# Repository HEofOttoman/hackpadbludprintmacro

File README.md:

# HenryWau's BludPad

* Keyboard Maintainer: [Henry Wauzivuff](https://github.com/heofottoman)

This is my very first macropad (and hardware project!) made for Hackpad. I designed it to be optimised for my little desk, being long and narrow, and also having a pretty cool pcb :>

Currently, the firmware binds the keys to Ctrl Z, numpad 1,3,7 & mswhl up/down, designed to help me with creative software, Blender specifically.

## Specifications
### BOM
- 1x Seeed Xiao RP4020
- 1x EC11 Rotary Encoder
- 4x Cherry MX switches
- 4x Blank Keycaps
- 4x SK6812 MINI-E LEDs
- 4x Screws

### Others
- Custom PCB
- QMK Firmware
- Case.STL

### Schematic
 
https://cdn.hackclub.com/019d466b-ad1f-7994-9d12-ee104b858810/image.png

### PCB

Dimensions at max: 38.496 x 97.794 mm
Top left corner to USB - 7.452 mm

Keyhole dimensions:
x = 2.635
y = 0.233

### Case

## References 
A list of the resources I used to hopefully help others and keep their own piece of sanity where I've lost it..

- [Xiao RP2040 Pin Reference](https://wiki.seeedstudio.com/XIAO-RP2040/) - Used the GPIO pins in the table provided for firmware code 
- [Legacy Blueprint Hackpad Guide](https://web.archive.org/web/20251224215247/https://blueprint.hackclub.com/hackpad/index.md) - https://web.archive.org/web/20251224215247/https://blueprint.hackclub.com/hackpad/index.md
- [Porting your keyboard to qmk](https://docs.qmk.fm/porting_your_keyboard_to_qmk)
- [Hackpad Github](https://github.com/hackclub/hackpad/) - Filled with examples of other macropads
- For the plate: [Keyboard Layout Editor](https://www.keyboard-layout-editor.com) & [Ai03's plate editor](https://kbplate.ai03.com)

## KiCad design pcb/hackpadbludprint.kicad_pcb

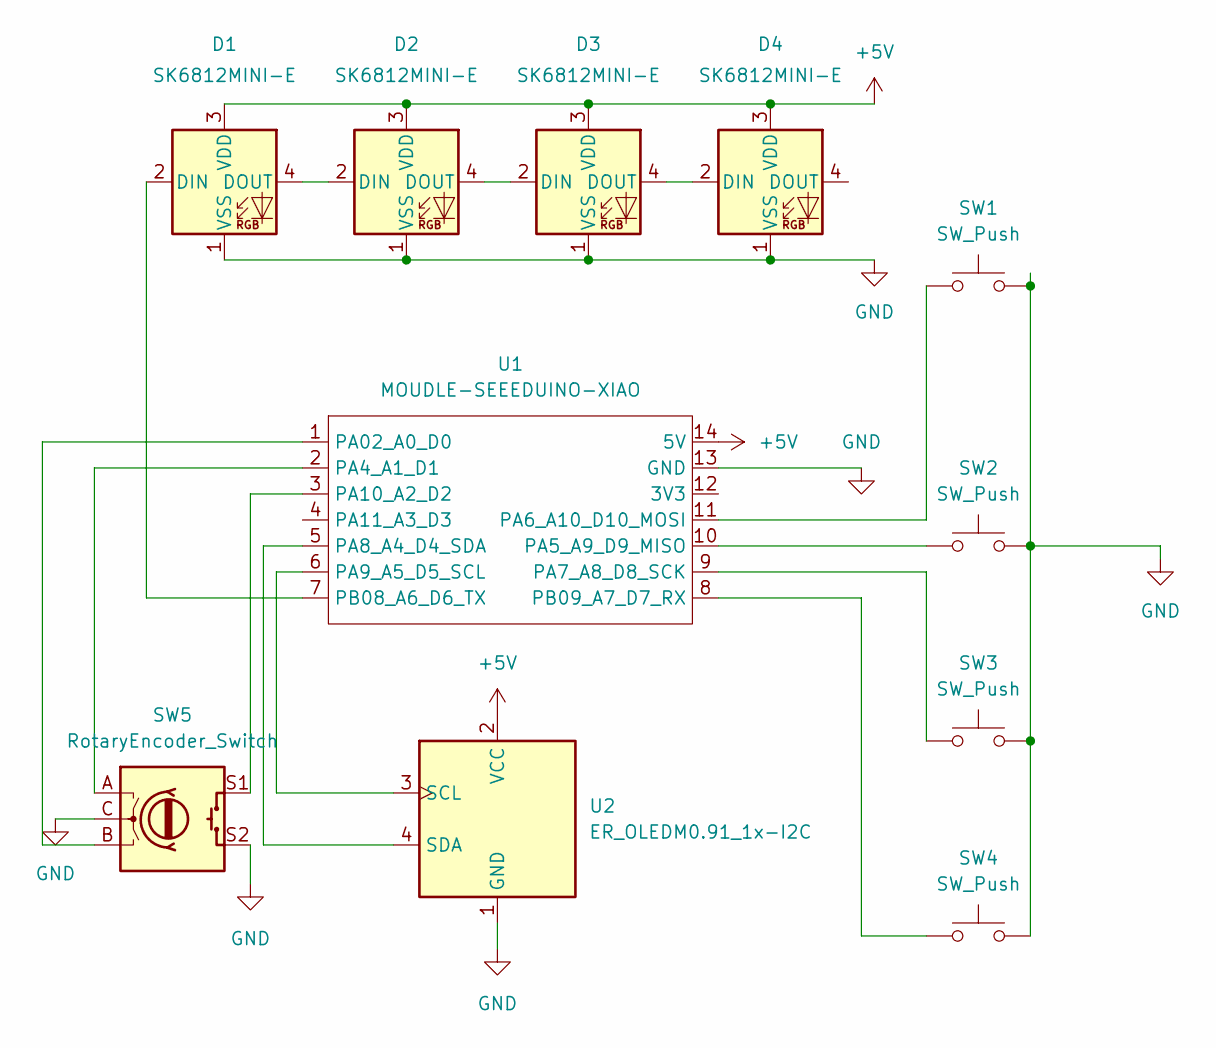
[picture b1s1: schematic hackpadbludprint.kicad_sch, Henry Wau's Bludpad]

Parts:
D1, D2, D3, D4: SK6812MINI-E; LED_SK6812MINI-E_3.2x2.8mm_P1.5mm_ReverseMount
SW1, SW2, SW3, SW4: SW_Push; SW_Cherry_MX_1.00u_PCB
SW5: RotaryEncoder_Switch; RotaryEncoder_Alps_EC11E-Switch_Vertical_H20mm
U1: MOUDLE-SEEEDUINO-XIAO; XIAO-Generic-Hybrid-14P-2.54-21X17.8MM
U2: ER_OLEDM0.91_1x-I2C

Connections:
+5V: D1.3 (VDD), D2.3 (VDD), D3.3 (VDD), D4.3 (VDD), U1.14 (5V), U2.2 (VCC)
GND: D1.1 (VSS), D2.1 (VSS), D3.1 (VSS), D4.1 (VSS), SW1.2, SW2.2, SW3.2, SW4.2, SW5.C, SW5.S2, U1.13 (GND), U2.1 (GND)
unnamed: D1.2 (DIN), U1.7 (PB08_A6_D6_TX)
unnamed: D1.4 (DOUT), D2.2 (DIN)
unnamed: D2.4 (DOUT), D3.2 (DIN)
unnamed: D3.4 (DOUT), D4.2 (DIN)
unnamed: SW5.B, U1.1 (PA02_A0_D0)
unnamed: SW5.A, U1.2 (PA4_A1_D1)
unnamed: SW2.1, U1.10 (PA5_A9_D9_MISO)
unnamed: SW1.1, U1.11 (PA6_A10_D10_MOSI)
unnamed: SW3.1, U1.9 (PA7_A8_D8_SCK)
unnamed: U1.5 (PA8_A4_D4_SDA), U2.4 (SDA)
unnamed: U1.6 (PA9_A5_D5_SCL), U2.3 (SCL)
unnamed: SW5.S1, U1.3 (PA10_A2_D2)
unnamed: SW4.1, U1.8 (PB09_A7_D7_RX)

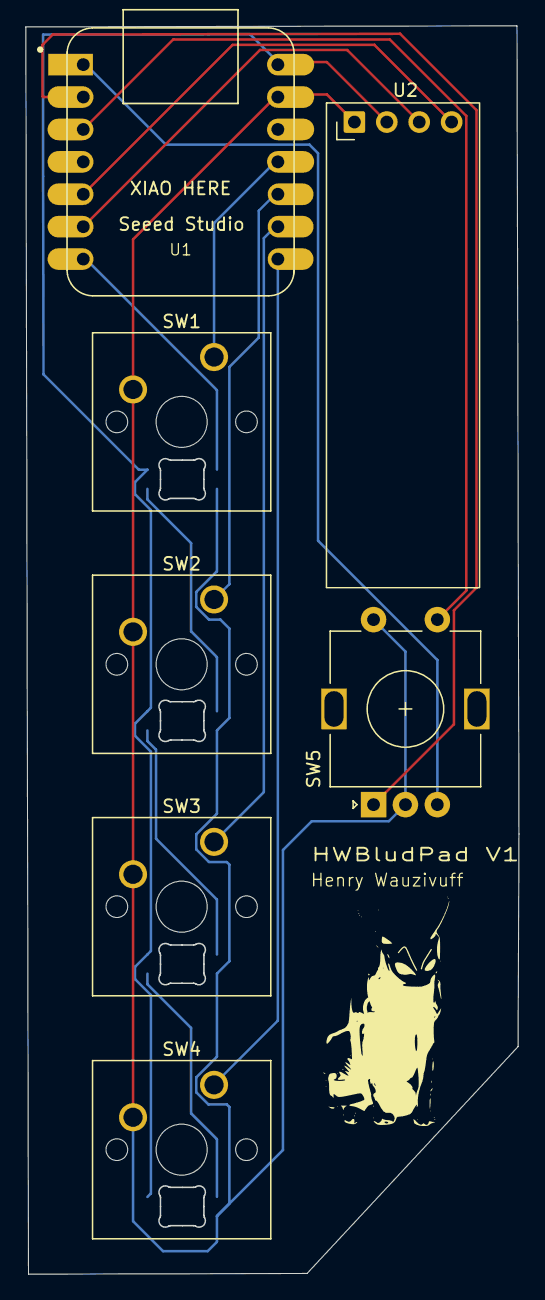
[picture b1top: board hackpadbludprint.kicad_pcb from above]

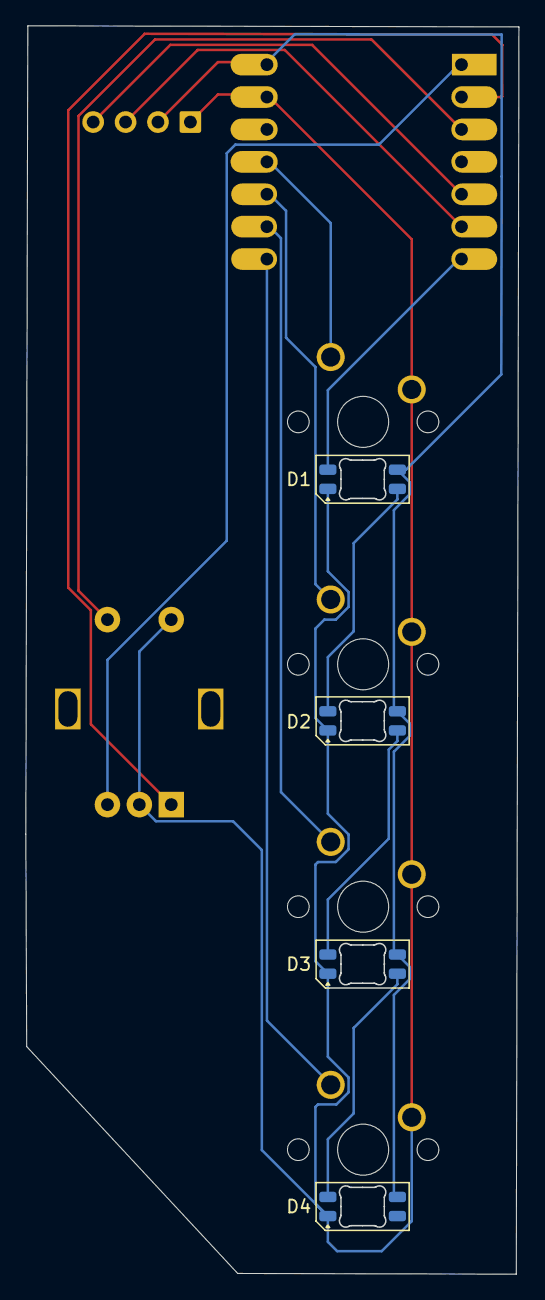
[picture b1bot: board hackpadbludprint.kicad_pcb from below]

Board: 2 copper layers, 38.6 x 97.8 mm, 11 parts (4 on the bottom side), 15 nets.

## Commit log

2026-03-30 Stretch 1
    - Schematic
    - PCB
2026-03-31 Reorganizing files
2026-03-31 STRETCH 3!!!!
    - board looking nice
    - Tysm jame
2026-03-31 Deleted unused kicadproj
    - Readme
    - Added lawrence silksreen icon
    - FIRMWARE moved here from home qmk folder in /users
2026-03-31 making firmware
    - moved rules.mk
    - keyboard.json in editing
2026-04-01 keyboard pins wrong
    they're very wrong
2026-04-01 Changed pins to match gpio
    - Schematic img added
    - Readme improved
    - Keyboard pins modded
2026-04-01 FRIDGEE
2026-04-01 GOGOGOGOGO
    GERBERS
2026-04-01 README POLISH
2026-04-01 TRYING TO FIX FIRMWARE
    - Changed pcb silkscreen
    - Moved readmes
2026-04-01 Changed image
    - Trying to fix firmware
    - Encoder coding
    - PCB cad file added
2026-04-01 Managed to compile .uf2 !!!
    - Deleted keyboard.h
    - Understand keymap.c now
    - Added the .uf2 file
2026-04-02 Updated ze gerbers with minibridge
2026-04-02 Finished case
    - CASEPLATE
    - Readme updated
    - Full cad
2026-04-02 Updated firmware YES
    YAYAYAYA
2026-04-02 Another archive file
2026-05-30 updated silkcreen and gerbers
    new gerbers and UHH silkscreen art
2026-05-30 okay nvm fixed silkscreen more
    Silkscreen shouldn't go over the copper pads or the through holes for that matter. I hope this'll be OK 😭
2026-06-01 i dont need this version of the gerbers anymore
    remove 'gerbers-v1' unzipped folder
